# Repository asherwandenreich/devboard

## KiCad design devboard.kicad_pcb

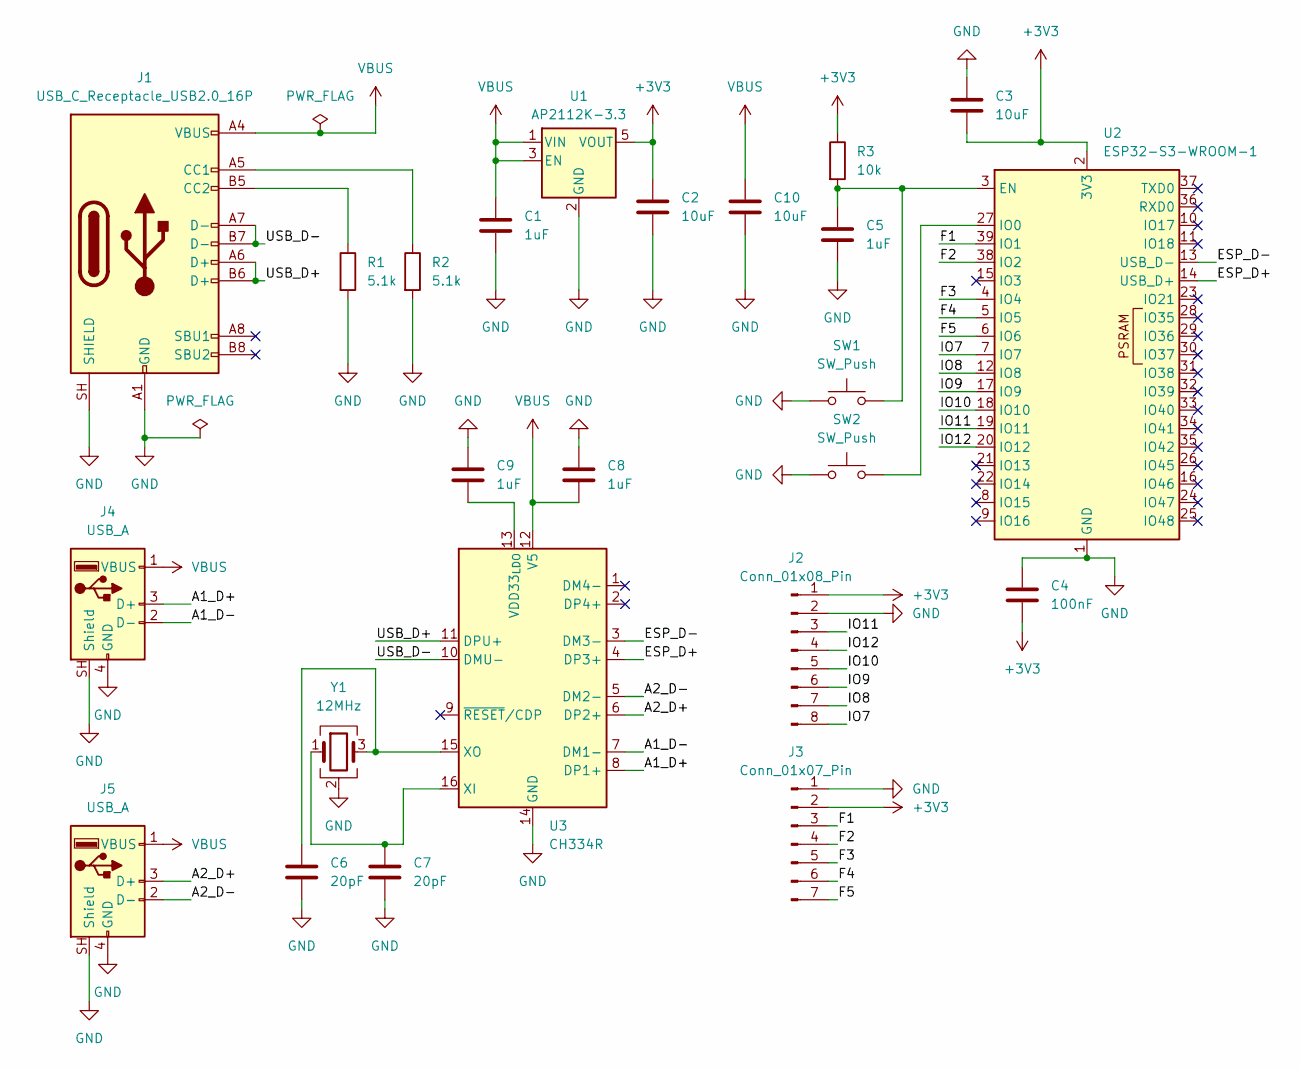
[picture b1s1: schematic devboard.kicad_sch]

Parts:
C1, C5, C8, C9: 1uF; C_0805_2012Metric
C2, C3, C10: 10uF; C_0805_2012Metric
C4: 100nF; C_0805_2012Metric
C6, C7: 20pF; C_0805_2012Metric
J1: USB_C_Receptacle_USB2.0_16P; USB_C_Receptacle_HRO_TYPE-C-31-M-12
J2: Conn_01x08_Pin; PinHeader_1x08_P2.54mm_Vertical
J3: Conn_01x07_Pin; PinHeader_1x07_P2.54mm_Vertical
J4, J5: USB_A; USB_A_Molex_67643_Horizontal
R1, R2: 5.1k; R_0805_2012Metric
R3: 10k; R_0805_2012Metric
SW1, SW2: SW_Push; SW_SPST_TL3342
U1: AP2112K-3.3; SOT-23-5
U2: ESP32-S3-WROOM-1
U3: CH334R; QSOP-16_3.9x4.9mm_P0.635mm
Y1: 12MHz; Crystal_SMD_3225-4Pin_3.2x2.5mm

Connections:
+3V3: C2.1, C3.2, C4.2, J2.1, J3.2, R3.1, U1.5 (VOUT), U2.2 (3V3)
/A1_D+: J4.3 (D+), U3.8 (DP1+)
/A1_D-: J4.2 (D-), U3.7 (DM1-)
/A2_D+: J5.3 (D+), U3.6 (DP2+)
/A2_D-: J5.2 (D-), U3.5 (DM2-)
/ESP_D+: U2.14 (USB_D+), U3.4 (DP3+)
/ESP_D-: U2.13 (USB_D-), U3.3 (DM3-)
/F1: J3.3, U2.39 (IO1)
/F2: J3.4, U2.38 (IO2)
/F3: J3.5, U2.4 (IO4)
/F4: J3.6, U2.5 (IO5)
/F5: J3.7, U2.6 (IO6)
/IO7: J2.8, U2.7 (IO7)
/IO8: J2.7, U2.12 (IO8)
/IO9: J2.6, U2.17 (IO9)
/IO10: J2.5, U2.18 (IO10)
/IO11: J2.3, U2.19 (IO11)
/IO12: J2.4, U2.20 (IO12)
/USB_D+: J1.A6 (D+), J1.B6 (D+), U3.11 (DPU+)
/USB_D-: J1.A7 (D-), J1.B7 (D-), U3.10 (DMU-)
GND: C1.2, C2.2, C3.1, C4.1, C5.2, C6.1, C7.2, C8.1, C9.1, C10.2, J1.A1 (GND), J1.A12 (GND), J1.B1 (GND), J1.B12 (GND), J1.SH (SHIELD), J2.2, J3.1, J4.4 (GND), J4.SH (Shield), J5.4 (GND), J5.SH (Shield), R1.2, R2.2, SW1.1, SW2.1, U1.2 (GND), U2.1 (GND), U2.40 (GND), U2.41 (GND), U3.14 (GND), Y1.2 (G), Y1.4 (G)
unnamed: J1.A5 (CC1), R2.1
unnamed: J1.B5 (CC2), R1.1
unnamed: C5.1, R3.2, SW1.2, U2.3 (EN)
unnamed: SW2.2, U2.27 (IO0)
unnamed: C9.2, U3.13 (VDD33_{LDO})
unnamed: C7.1, U3.16 (XI), Y1.1
unnamed: C6.2, U3.15 (XO), Y1.3
VBUS: C1.1, C8.2, C10.1, J1.A4 (VBUS), J1.A9 (VBUS), J1.B4 (VBUS), J1.B9 (VBUS), J4.1 (VBUS), J5.1 (VBUS), U1.1 (VIN), U1.3 (EN), U3.12 (V5)

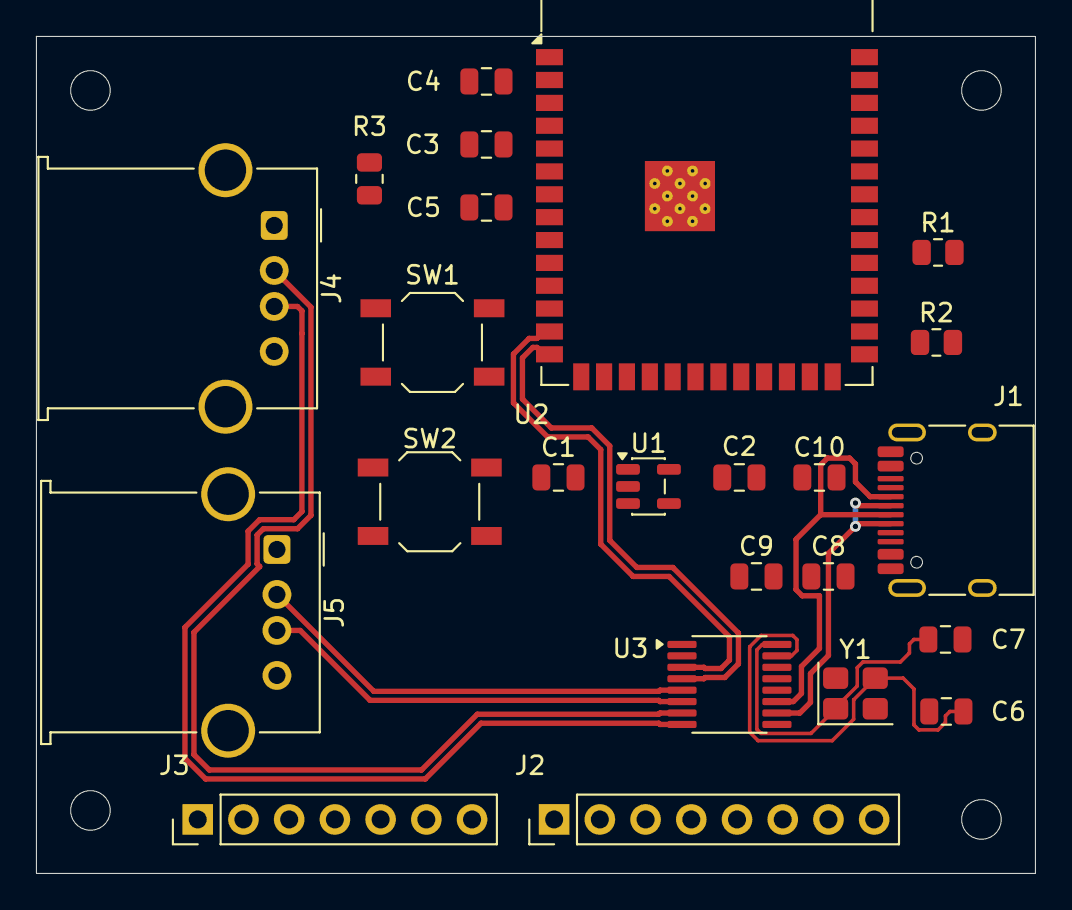
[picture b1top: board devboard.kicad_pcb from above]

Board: 2 copper layers, 55.5 x 46.5 mm, 28 parts (0 on the bottom side), 29 nets.

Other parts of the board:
H1, H2, H3, H4: MountingHole_2.2mm_M2
